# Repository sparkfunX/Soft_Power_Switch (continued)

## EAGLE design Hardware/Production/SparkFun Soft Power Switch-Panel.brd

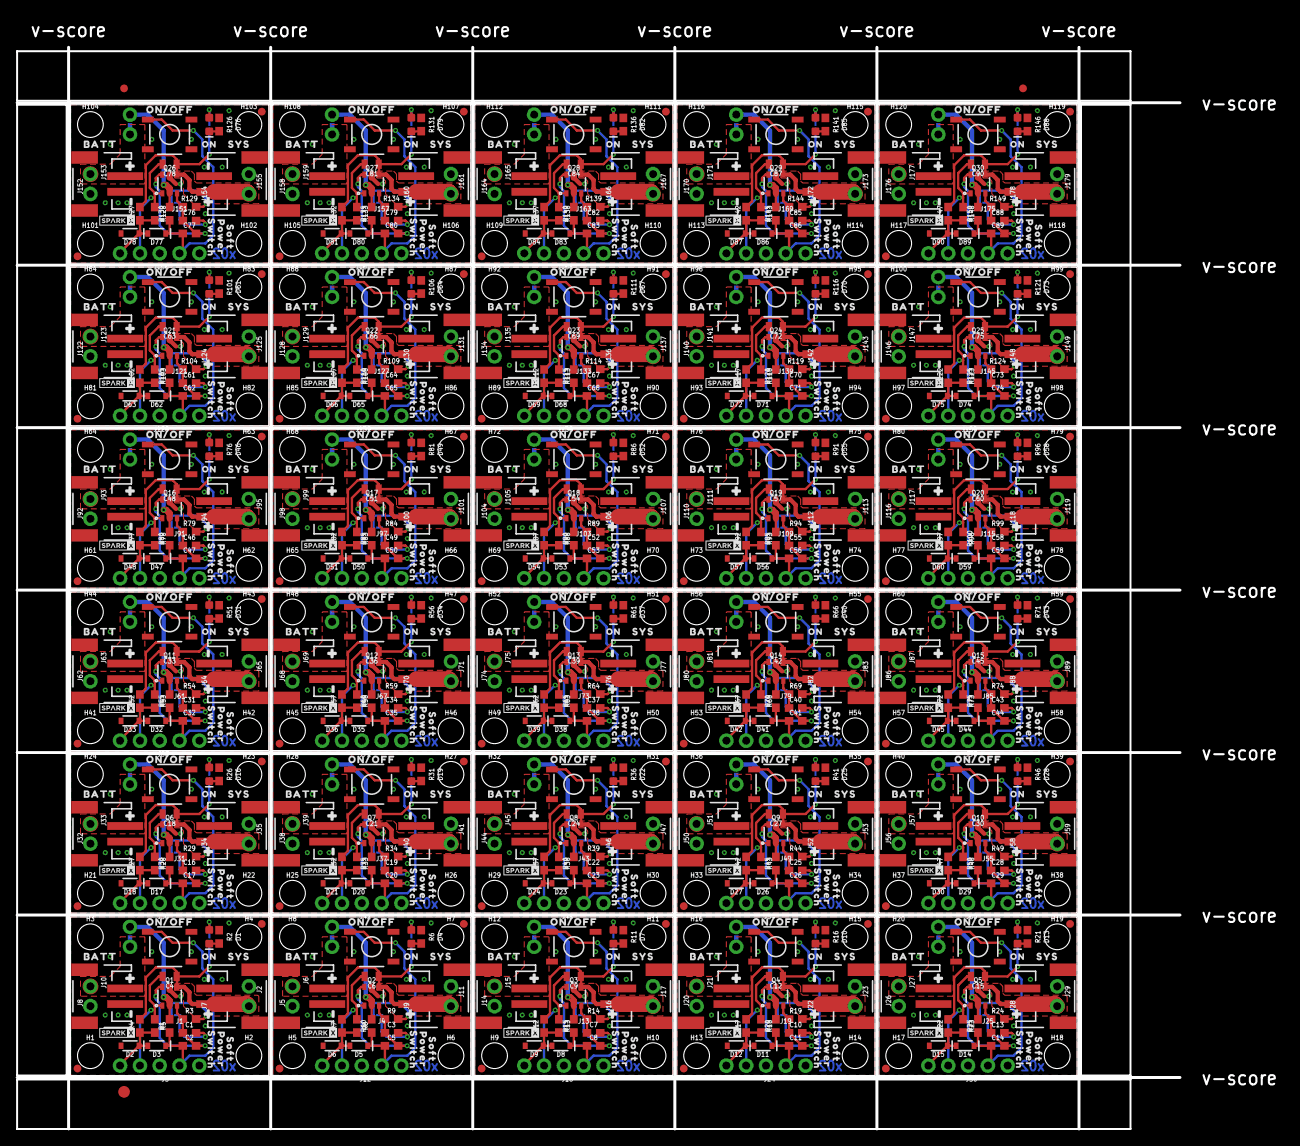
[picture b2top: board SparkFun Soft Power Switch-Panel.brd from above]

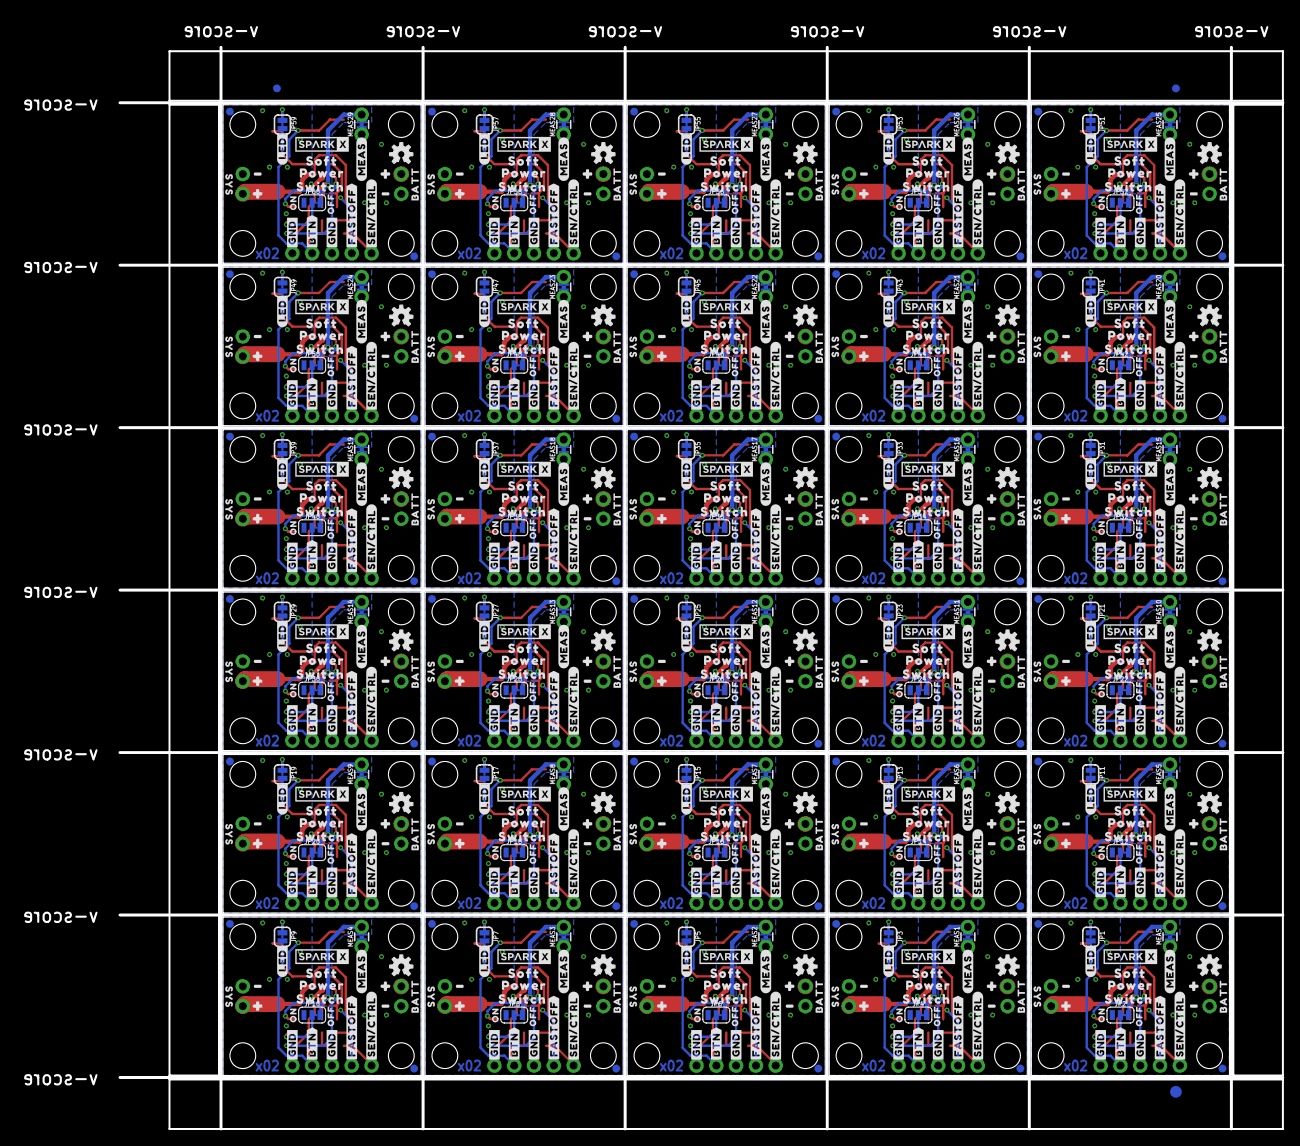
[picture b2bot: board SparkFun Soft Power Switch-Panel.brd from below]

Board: 2 copper layers, 149.1 x 138.7 mm, 1866 parts (753 on the bottom side), 330 nets.

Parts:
C1, C2, C3, C5, C7, C8, C10, C11, C13, C14, C16, C17, C19, C20, C22, C23, C25, C26, C28, C29, C31, C32, C34, C35, C37, C38, C40, C41, C43, C44, C46, C47, C49, C50, C52, C53, C55, C56, C58, C59, C61, C62, C64, C65, C67, C68, C70, C71, C73, C74, C76, C77, C79, C80, C82, C83, C85, C86, C88, C89: 0.1uF; 0603
C4, C6, C9, C12, C15, C18, C21, C24, C27, C30, C33, C36, C39, C42, C45, C48, C51, C54, C57, C60, C63, C66, C69, C72, C75, C78, C81, C84, C87, C90: 22uF; 0805
D1, D4, D7, D10, D13, D16, D19, D22, D25, D28, D31, D34, D37, D40, D43, D46, D49, D52, D55, D58, D61, D64, D67, D70, D73, D76, D79, D82, D85, D88: Power; LED-0603
D2, D6, D9, D12, D15, D18, D21, D24, D27, D30, D33, D36, D39, D42, D45, D48, D51, D54, D57, D60, D63, D66, D69, D72, D75, D78, D81, D84, D87, D90: 3.3V; SOD-323
D3, D5, D8, D11, D14, D17, D20, D23, D26, D29, D32, D35, D38, D41, D44, D47, D50, D53, D56, D59, D62, D65, D68, D71, D74, D77, D80, D83, D86, D89: 250mA/100V; SOD-323
E$1, E$2, E$3, E$4: FIDUCIAL-1X2
E$5, E$6: FIDUCIAL-1.5X3
FD1, FD2, FD3, FD4, FD5, FD6, FD7, FD8, FD9, FD10, FD11, FD12, FD13, FD14, FD15, FD16, FD17, FD18, FD19, FD20, FD21, FD22, FD23, FD24, FD25, FD26, FD27, FD28, FD29, FD30, FD31, FD32, FD33, FD34, FD35, FD36, FD37, FD38, FD39, FD40, FD41, FD42, FD43, FD44, FD45, FD46, FD47, FD48, FD49, FD50, FD51, FD52, FD53, FD54, FD55, FD56, FD57, FD58, FD59, FD60, FD61, FD62, FD63, FD64, FD65, FD66, FD67, FD68, FD69, FD70, FD71, FD72, FD73, FD74, FD75, FD76, FD77, FD78, FD79, FD80, FD81, FD82, FD83, FD84, FD85, FD86, FD87, FD88, FD89, FD90, FD91, FD92, FD93, FD94, FD95, FD96, FD97, FD98, FD99, FD100, FD101, FD102, FD103, FD104, FD105, FD106, FD107, FD108, FD109, FD110, FD111, FD112, FD113, FD114, FD115, FD116, FD117, FD118, FD119, FD120: FIDUCIAL1X2; FIDUCIAL-1X2
H1, H2, H3, H4, H5, H6, H7, H8, H9, H10, H11, H12, H13, H14, H15, H16, H17, H18, H19, H20, H21, H22, H23, H24, H25, H26, H27, H28, H29, H30, H31, H32, H33, H34, H35, H36, H37, H38, H39, H40, H41, H42, H43, H44, H45, H46, H47, H48, H49, H50, H51, H52, H53, H54, H55, H56, H57, H58, H59, H60, H61, H62, H63, H64, H65, H66, H67, H68, H69, H70, H71, H72, H73, H74, H75, H76, H77, H78, H79, H80, H81, H82, H83, H84, H85, H86, H87, H88, H89, H90, H91, H92, H93, H94, H95, H96, H97, H98, H99, H100, H101, H102, H103, H104, H105, H106, H107, H108, H109, H110, H111, H112, H113, H114, H115, H116, H117, H118, H119, H120: STAND-OFF
J1, J4, J13, J19, J25, J31, J37, J43, J49, J55, J61, J67, J73, J79, J85, J91, J97, J103, J109, J115, J121, J127, J133, J139, J145, J151, J157, J163, J169, J175: Ext Button; 1X02_NO_SILK
J2, J5, J8, J11, J14, J17, J20, J23, J26, J29, J32, J35, J38, J41, J44, J47, J50, J53, J56, J59, J62, J65, J68, J71, J74, J77, J80, J83, J86, J89, J92, J95, J98, J101, J104, J107, J110, J113, J116, J119, J122, J125, J128, J131, J134, J137, J140, J143, J146, J149, J152, J155, J158, J161, J164, J167, J170, J173, J176, J179: JST-2-SMD
J3, J12, J18, J24, J30, J36, J42, J48, J54, J60, J66, J72, J78, J84, J90, J96, J102, J108, J114, J120, J126, J132, J138, J144, J150, J156, J162, J168, J174, J180: 1X03_NO_SILK
J6, J10, J15, J21, J27, J33, J39, J45, J51, J57, J63, J69, J75, J81, J87, J93, J99, J105, J111, J117, J123, J129, J135, J141, J147, J153, J159, J165, J171, J177: 1X02_NO_SILK
J7, J9, J16, J22, J28, J34, J40, J46, J52, J58, J64, J70, J76, J82, J88, J94, J100, J106, J112, J118, J124, J130, J136, J142, J148, J154, J160, J166, J172, J178: System Power; 1X02_NO_SILK
JP1, JP3, JP5, JP7, JP9, JP11, JP13, JP15, JP17, JP19, JP21, JP23, JP25, JP27, JP29, JP31, JP33, JP35, JP37, JP39, JP41, JP43, JP45, JP47, JP49, JP51, JP53, JP55, JP57, JP59: SMT-JUMPER_2_NC_TRACE_SILK
JP2, JP4, JP6, JP8, JP10, JP12, JP14, JP16, JP18, JP20, JP22, JP24, JP26, JP28, JP30, JP32, JP34, JP36, JP38, JP40, JP42, JP44, JP46, JP48, JP50, JP52, JP54, JP56, JP58, JP60: SMT-JUMPER_3_1-NC_TRACE_SILK
LOGO1, LOGO2, LOGO3, LOGO4, LOGO5, LOGO6, LOGO7, LOGO8, LOGO9, LOGO10, LOGO11, LOGO12, LOGO13, LOGO14, LOGO15, LOGO16, LOGO17, LOGO18, LOGO19, LOGO20, LOGO21, LOGO22, LOGO23, LOGO24, LOGO25, LOGO26, LOGO27, LOGO28, LOGO29, LOGO30: OSHW-LOGOS; OSHW-LOGO-S
MEAS, MEAS1, MEAS2, MEAS3, MEAS4, MEAS5, MEAS6, MEAS7, MEAS8, MEAS9, MEAS10, MEAS11, MEAS12, MEAS13, MEAS14, MEAS15, MEAS16, MEAS17, MEAS18, MEAS19, MEAS20, MEAS21, MEAS22, MEAS23, MEAS24, MEAS25, MEAS26, MEAS27, MEAS28, MEAS29: COMBO-JUMPER_2_NC_TRACE
Q1, Q2, Q3, Q4, Q5, Q6, Q7, Q8, Q9, Q10, Q11, Q12, Q13, Q14, Q15, Q16, Q17, Q18, Q19, Q20, Q21, Q22, Q23, Q24, Q25, Q26, Q27, Q28, Q29, Q30: SIL2308-TP; SOT26
R1, R4, R7, R10, R12, R15, R17, R20, R22, R25, R27, R30, R32, R35, R37, R40, R42, R45, R47, R50, R52, R55, R57, R60, R62, R65, R67, R70, R72, R75, R77, R80, R82, R85, R87, R90, R92, R95, R97, R100, R102, R105, R107, R110, R112, R115, R117, R120, R122, R125, R127, R130, R132, R135, R137, R140, R142, R145, R147, R150: 10k; 0603
R2, R6, R11, R16, R21, R26, R31, R36, R41, R46, R51, R56, R61, R66, R71, R76, R81, R86, R91, R96, R101, R106, R111, R116, R121, R126, R131, R136, R141, R146: 1k; 0603
R3, R9, R14, R19, R24, R29, R34, R39, R44, R49, R54, R59, R64, R69, R74, R79, R84, R89, R94, R99, R104, R109, R114, R119, R124, R129, R134, R139, R144, R149: 100k; 0603
R5, R8, R13, R18, R23, R28, R33, R38, R43, R48, R53, R58, R63, R68, R73, R78, R83, R88, R93, R98, R103, R108, R113, R118, R123, R128, R133, R138, R143, R148: 300k; 0603
S1, S2, S3, S4, S5, S6, S7, S8, S9, S10, S11, S12, S13, S14, S15, S16, S17, S18, S19, S20, S21, S22, S23, S24, S25, S26, S27, S28, S29, S30: Power; TACTILE_SWITCH_SMD_5.2MM
U$1, U$32, U$63, U$94, U$125, U$156, U$187, U$218, U$249, U$280, U$311, U$342, U$373, U$404, U$435, U$466, U$497, U$528, U$559, U$590, U$621, U$652, U$683, U$714, U$745, U$776, U$807, U$838, U$869, U$900: SPARKX-LOGO3; SPARKX-SMALL
U$2, U$33, U$64, U$95, U$126, U$157, U$188, U$219, U$250, U$281, U$312, U$343, U$374, U$405, U$436, U$467, U$498, U$529, U$560, U$591, U$622, U$653, U$684, U$715, U$746, U$777, U$808, U$839, U$870, U$901: #BTN#2
U$3, U$4, U$34, U$35, U$65, U$66, U$96, U$97, U$127, U$128, U$158, U$159, U$189, U$190, U$220, U$221, U$251, U$252, U$282, U$283, U$313, U$314, U$344, U$345, U$375, U$376, U$406, U$407, U$437, U$438, U$468, U$469, U$499, U$500, U$530, U$531, U$561, U$562, U$592, U$593, U$623, U$624, U$654, U$655, U$685, U$686, U$716, U$717, U$747, U$748, U$778, U$779, U$809, U$810, U$840, U$841, U$871, U$872, U$902, U$903: #GND#0
U$5, U$36, U$67, U$98, U$129, U$160, U$191, U$222, U$253, U$284, U$315, U$346, U$377, U$408, U$439, U$470, U$501, U$532, U$563, U$594, U$625, U$656, U$687, U$718, U$749, U$780, U$811, U$842, U$873, U$904: #SEN#CTRL#1
U$6, U$37, U$68, U$99, U$130, U$161, U$192, U$223, U$254, U$285, U$316, U$347, U$378, U$409, U$440, U$471, U$502, U$533, U$564, U$595, U$626, U$657, U$688, U$719, U$750, U$781, U$812, U$843, U$874, U$905: ON#OFF0
U$7, U$29, U$38, U$60, U$69, U$91, U$100, U$122, U$131, U$153, U$162, U$184, U$193, U$215, U$224, U$246, U$255, U$277, U$286, U$308, U$317, U$339, U$348, U$370, U$379, U$401, U$410, U$432, U$441, U$463, U$472, U$494, U$503, U$525, U$534, U$556, U$565, U$587, U$596, U$618, U$627, U$649, U$658, U$680, U$689, U$711, U$720, U$742, U$751, U$773, U$782, U$804, U$813, U$835, U$844, U$866, U$875, U$897, U$906, U$928: BATT0
U$8, U$31, U$39, U$61, U$70, U$92, U$101, U$123, U$132, U$154, U$163, U$185, U$194, U$216, U$225, U$247, U$256, U$278, U$287, U$309, U$318, U$340, U$349, U$371, U$380, U$402, U$411, U$433, U$442, U$464, U$473, U$495, U$504, U$526, U$535, U$557, U$566, U$588, U$597, U$619, U$628, U$650, U$659, U$681, U$690, U$712, U$721, U$743, U$752, U$774, U$783, U$805, U$814, U$836, U$845, U$867, U$876, U$898, U$907, U$929: SYS1
U$9, U$10, U$14, U$22, U$40, U$41, U$48, U$50, U$71, U$72, U$79, U$81, U$102, U$103, U$110, U$112, U$133, U$134, U$141, U$143, U$164, U$165, U$172, U$174, U$195, U$196, U$203, U$205, U$226, U$227, U$234, U$236, U$257, U$258, U$265, U$267, U$288, U$289, U$296, U$298, U$319, U$320, U$327, U$329, U$350, U$351, U$358, U$360, U$381, U$382, U$389, U$391, U$412, U$413, U$420, U$422, U$443, U$444, U$451, U$453, U$474, U$475, U$482, U$484, U$505, U$506, U$513, U$515, U$536, U$537, U$544, U$546, U$567, U$568, U$575, U$577, U$598, U$599, U$606, U$608, U$629, U$630, U$637, U$639, U$660, U$661, U$668, U$670, U$691, U$692, U$699, U$701, U$722, U$723, U$730, U$732, U$753, U$754, U$761, U$763, U$784, U$785, U$792, U$794, U$815, U$816, U$823, U$825, U$846, U$847, U$854, U$856, U$877, U$878, U$885, U$887, U$908, U$909, U$916, U$918: #0
U$11, U$12, U$20, U$23, U$42, U$43, U$49, U$51, U$73, U$74, U$80, U$82, U$104, U$105, U$111, U$113, U$135, U$136, U$142, U$144, U$166, U$167, U$173, U$175, U$197, U$198, U$204, U$206, U$228, U$229, U$235, U$237, U$259, U$260, U$266, U$268, U$290, U$291, U$297, U$299, U$321, U$322, U$328, U$330, U$352, U$353, U$359, U$361, U$383, U$384, U$390, U$392, U$414, U$415, U$421, U$423, U$445, U$446, U$452, U$454, U$476, U$477, U$483, U$485, U$507, U$508, U$514, U$516, U$538, U$539, U$545, U$547, U$569, U$570, U$576, U$578, U$600, U$601, U$607, U$609, U$631, U$632, U$638, U$640, U$662, U$663, U$669, U$671, U$693, U$694, U$700, U$702, U$724, U$725, U$731, U$733, U$755, U$756, U$762, U$764, U$786, U$787, U$793, U$795, U$817, U$818, U$824, U$826, U$848, U$849, U$855, U$857, U$879, U$880, U$886, U$888, U$910, U$911, U$917, U$919: #1
U$13, U$44, U$75, U$106, U$137, U$168, U$199, U$230, U$261, U$292, U$323, U$354, U$385, U$416, U$447, U$478, U$509, U$540, U$571, U$602, U$633, U$664, U$695, U$726, U$757, U$788, U$819, U$850, U$881, U$912: #MEAS#0
U$15, U$62, U$93, U$124, U$155, U$186, U$217, U$248, U$279, U$310, U$341, U$372, U$403, U$434, U$465, U$496, U$527, U$558, U$589, U$620, U$651, U$682, U$713, U$744, U$775, U$806, U$837, U$868, U$899, U$930: SPARKX-LOGO2; SPARKX-TINY
U$16, U$57, U$88, U$119, U$150, U$181, U$212, U$243, U$274, U$305, U$336, U$367, U$398, U$429, U$460, U$491, U$522, U$553, U$584, U$615, U$646, U$677, U$708, U$739, U$770, U$801, U$832, U$863, U$894, U$925: OFF1
U$17, U$45, U$76, U$107, U$138, U$169, U$200, U$231, U$262, U$293, U$324, U$355, U$386, U$417, U$448, U$479, U$510, U$541, U$572, U$603, U$634, U$665, U$696, U$727, U$758, U$789, U$820, U$851, U$882, U$913: SWITCH2
U$18, U$25, U$46, U$58, U$77, U$89, U$108, U$120, U$139, U$151, U$170, U$182, U$201, U$213, U$232, U$244, U$263, U$275, U$294, U$306, U$325, U$337, U$356, U$368, U$387, U$399, U$418, U$430, U$449, U$461, U$480, U$492, U$511, U$523, U$542, U$554, U$573, U$585, U$604, U$616, U$635, U$647, U$666, U$678, U$697, U$709, U$728, U$740, U$759, U$771, U$790, U$802, U$821, U$833, U$852, U$864, U$883, U$895, U$914, U$926: ON0
U$19, U$47, U$78, U$109, U$140, U$171, U$202, U$233, U$264, U$295, U$326, U$357, U$388, U$419, U$450, U$481, U$512, U$543, U$574, U$605, U$636, U$667, U$698, U$729, U$760, U$791, U$822, U$853, U$884, U$915: #LED#0
U$21, U$55, U$86, U$117, U$148, U$179, U$210, U$241, U$272, U$303, U$334, U$365, U$396, U$427, U$458, U$489, U$520, U$551, U$582, U$613, U$644, U$675, U$706, U$737, U$768, U$799, U$830, U$861, U$892, U$923: SOFT_0
U$24, U$56, U$87, U$118, U$149, U$180, U$211, U$242, U$273, U$304, U$335, U$366, U$397, U$428, U$459, U$490, U$521, U$552, U$583, U$614, U$645, U$676, U$707, U$738, U$769, U$800, U$831, U$862, U$893, U$924: POWER_1
U$26, U$59, U$90, U$121, U$152, U$183, U$214, U$245, U$276, U$307, U$338, U$369, U$400, U$431, U$462, U$493, U$524, U$555, U$586, U$617, U$648, U$679, U$710, U$741, U$772, U$803, U$834, U$865, U$896, U$927: #FASTOFF#0
U$27, U$52, U$83, U$114, U$145, U$176, U$207, U$238, U$269, U$300, U$331, U$362, U$393, U$424, U$455, U$486, U$517, U$548, U$579, U$610, U$641, U$672, U$703, U$734, U$765, U$796, U$827, U$858, U$889, U$920: SOFT0
U$28, U$53, U$84, U$115, U$146, U$177, U$208, U$239, U$270, U$301, U$332, U$363, U$394, U$425, U$456, U$487, U$518, U$549, U$580, U$611, U$642, U$673, U$704, U$735, U$766, U$797, U$828, U$859, U$890, U$921: POWER1
U$30, U$54, U$85, U$116, U$147, U$178, U$209, U$240, U$271, U$302, U$333, U$364, U$395, U$426, U$457, U$488, U$519, U$550, U$581, U$612, U$643, U$674, U$705, U$736, U$767, U$798, U$829, U$860, U$891, U$922: SWITCH_2

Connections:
FAST_OFF: C4.2, J3.2, Q1.G1, R5.1
FAST_OFF1: C6.2, J12.2, Q2.G1, R8.1
FAST_OFF2: C9.2, J18.2, Q3.G1, R13.1
FAST_OFF3: C12.2, J24.2, Q4.G1, R18.1
FAST_OFF4: C15.2, J30.2, Q5.G1, R23.1
FAST_OFF5: C18.2, J36.2, Q6.G1, R28.1
FAST_OFF6: C21.2, J42.2, Q7.G1, R33.1
FAST_OFF7: C24.2, J48.2, Q8.G1, R38.1
FAST_OFF8: C27.2, J54.2, Q9.G1, R43.1
FAST_OFF9: C30.2, J60.2, Q10.G1, R48.1
FAST_OFF10: C33.2, J66.2, Q11.G1, R53.1
FAST_OFF11: C36.2, J72.2, Q12.G1, R58.1
FAST_OFF12: C39.2, J78.2, Q13.G1, R63.1
FAST_OFF13: C42.2, J84.2, Q14.G1, R68.1
FAST_OFF14: C45.2, J90.2, Q15.G1, R73.1
FAST_OFF15: C48.2, J96.2, Q16.G1, R78.1
FAST_OFF16: C51.2, J102.2, Q17.G1, R83.1
FAST_OFF17: C54.2, J108.2, Q18.G1, R88.1
FAST_OFF18: C57.2, J114.2, Q19.G1, R93.1
FAST_OFF19: C60.2, J120.2, Q20.G1, R98.1
FAST_OFF20: C63.2, J126.2, Q21.G1, R103.1
FAST_OFF21: C66.2, J132.2, Q22.G1, R108.1
FAST_OFF22: C69.2, J138.2, Q23.G1, R113.1
FAST_OFF23: C72.2, J144.2, Q24.G1, R118.1
FAST_OFF24: C75.2, J150.2, Q25.G1, R123.1
FAST_OFF25: C78.2, J156.2, Q26.G1, R128.1
FAST_OFF26: C81.2, J162.2, Q27.G1, R133.1
FAST_OFF27: C84.2, J168.2, Q28.G1, R138.1
FAST_OFF28: C87.2, J174.2, Q29.G1, R143.1
FAST_OFF29: C90.2, J180.2, Q30.G1, R148.1
GND: D2.A, J1.2, J2.1, J3.1, J7.2, J8.1, J10.2, JP2.1, Q1.S1, R2.1, S1.3
GND1: D6.A, J4.2, J5.1, J6.2, J9.2, J11.1, J12.1, JP4.1, Q2.S1, R6.1, S2.3
GND2: D9.A, J13.2, J14.1, J15.2, J16.2, J17.1, J18.1, JP6.1, Q3.S1, R11.1, S3.3
GND3: D12.A, J19.2, J20.1, J21.2, J22.2, J23.1, J24.1, JP8.1, Q4.S1, R16.1, S4.3
GND4: D15.A, J25.2, J26.1, J27.2, J28.2, J29.1, J30.1, JP10.1, Q5.S1, R21.1, S5.3
GND5: D18.A, J31.2, J32.1, J33.2, J34.2, J35.1, J36.1, JP12.1, Q6.S1, R26.1, S6.3
GND6: D21.A, J37.2, J38.1, J39.2, J40.2, J41.1, J42.1, JP14.1, Q7.S1, R31.1, S7.3
GND7: D24.A, J43.2, J44.1, J45.2, J46.2, J47.1, J48.1, JP16.1, Q8.S1, R36.1, S8.3
GND8: D27.A, J49.2, J50.1, J51.2, J52.2, J53.1, J54.1, JP18.1, Q9.S1, R41.1, S9.3
GND9: D30.A, J55.2, J56.1, J57.2, J58.2, J59.1, J60.1, JP20.1, Q10.S1, R46.1, S10.3
GND10: D33.A, J61.2, J62.1, J63.2, J64.2, J65.1, J66.1, JP22.1, Q11.S1, R51.1, S11.3
GND11: D36.A, J67.2, J68.1, J69.2, J70.2, J71.1, J72.1, JP24.1, Q12.S1, R56.1, S12.3
GND12: D39.A, J73.2, J74.1, J75.2, J76.2, J77.1, J78.1, JP26.1, Q13.S1, R61.1, S13.3
GND13: D42.A, J79.2, J80.1, J81.2, J82.2, J83.1, J84.1, JP28.1, Q14.S1, R66.1, S14.3
GND14: D45.A, J85.2, J86.1, J87.2, J88.2, J89.1, J90.1, JP30.1, Q15.S1, R71.1, S15.3
GND15: D48.A, J91.2, J92.1, J93.2, J94.2, J95.1, J96.1, JP32.1, Q16.S1, R76.1, S16.3
GND16: D51.A, J97.2, J98.1, J99.2, J100.2, J101.1, J102.1, JP34.1, Q17.S1, R81.1, S17.3
GND17: D54.A, J103.2, J104.1, J105.2, J106.2, J107.1, J108.1, JP36.1, Q18.S1, R86.1, S18.3
GND18: D57.A, J109.2, J110.1, J111.2, J112.2, J113.1, J114.1, JP38.1, Q19.S1, R91.1, S19.3
GND19: D60.A, J115.2, J116.1, J117.2, J118.2, J119.1, J120.1, JP40.1, Q20.S1, R96.1, S20.3
GND20: D63.A, J121.2, J122.1, J123.2, J124.2, J125.1, J126.1, JP42.1, Q21.S1, R101.1, S21.3
GND21: D66.A, J127.2, J128.1, J129.2, J130.2, J131.1, J132.1, JP44.1, Q22.S1, R106.1, S22.3
GND22: D69.A, J133.2, J134.1, J135.2, J136.2, J137.1, J138.1, JP46.1, Q23.S1, R111.1, S23.3
GND23: D72.A, J139.2, J140.1, J141.2, J142.2, J143.1, J144.1, JP48.1, Q24.S1, R116.1, S24.3
GND24: D75.A, J145.2, J146.1, J147.2, J148.2, J149.1, J150.1, JP50.1, Q25.S1, R121.1, S25.3
GND25: D78.A, J151.2, J152.1, J153.2, J154.2, J155.1, J156.1, JP52.1, Q26.S1, R126.1, S26.3
GND26: D81.A, J157.2, J158.1, J159.2, J160.2, J161.1, J162.1, JP54.1, Q27.S1, R131.1, S27.3
GND27: D84.A, J163.2, J164.1, J165.2, J166.2, J167.1, J168.1, JP56.1, Q28.S1, R136.1, S28.3
GND28: D87.A, J169.2, J170.1, J171.2, J172.2, J173.1, J174.1, JP58.1, Q29.S1, R141.1, S29.3
GND29: D90.A, J175.2, J176.1, J177.2, J178.2, J179.1, J180.1, JP60.1, Q30.S1, R146.1, S30.3
unnamed: C1.2, JP2.2
unnamed: D1.A, JP1.1
unnamed: D4.C, R6.2
unnamed: C3.1, C5.2, Q2.D1, Q2.G2, R9.1
unnamed: D4.A, JP3.1
unnamed: D1.C, R2.2
unnamed: C3.2, JP4.2
unnamed: D7.C, R11.2
unnamed: C7.1, C8.2, Q3.D1, Q3.G2, R14.1
unnamed: D7.A, JP5.1
unnamed: C7.2, JP6.2
unnamed: D10.C, R16.2
unnamed: C10.1, C11.2, Q4.D1, Q4.G2, R19.1
unnamed: D10.A, JP7.1
unnamed: C1.1, C2.2, Q1.D1, Q1.G2, R3.1
unnamed: C10.2, JP8.2
unnamed: D13.C, R21.2
unnamed: C13.1, C14.2, Q5.D1, Q5.G2, R24.1
unnamed: D13.A, JP9.1
unnamed: C13.2, JP10.2
unnamed: D16.C, R26.2
unnamed: C16.1, C17.2, Q6.D1, Q6.G2, R29.1
unnamed: D16.A, JP11.1
unnamed: C16.2, JP12.2
unnamed: D19.C, R31.2
unnamed: C19.1, C20.2, Q7.D1, Q7.G2, R34.1
unnamed: D19.A, JP13.1
unnamed: C19.2, JP14.2
unnamed: D22.C, R36.2
unnamed: C22.1, C23.2, Q8.D1, Q8.G2, R39.1
unnamed: D22.A, JP15.1
unnamed: C22.2, JP16.2
unnamed: D25.C, R41.2
unnamed: C25.1, C26.2, Q9.D1, Q9.G2, R44.1
unnamed: D25.A, JP17.1
unnamed: C25.2, JP18.2
unnamed: D28.C, R46.2
unnamed: C28.1, C29.2, Q10.D1, Q10.G2, R49.1
unnamed: D28.A, JP19.1
unnamed: C28.2, JP20.2
unnamed: D31.C, R51.2
unnamed: C31.1, C32.2, Q11.D1, Q11.G2, R54.1
unnamed: D31.A, JP21.1
unnamed: C31.2, JP22.2
unnamed: D34.C, R56.2
unnamed: C34.1, C35.2, Q12.D1, Q12.G2, R59.1
unnamed: D34.A, JP23.1
unnamed: C34.2, JP24.2
unnamed: D37.C, R61.2
unnamed: C37.1, C38.2, Q13.D1, Q13.G2, R64.1
unnamed: D37.A, JP25.1
unnamed: C37.2, JP26.2
unnamed: D40.C, R66.2
unnamed: C40.1, C41.2, Q14.D1, Q14.G2, R69.1
unnamed: D40.A, JP27.1
unnamed: C40.2, JP28.2
unnamed: D43.C, R71.2
unnamed: C43.1, C44.2, Q15.D1, Q15.G2, R74.1
unnamed: D43.A, JP29.1
unnamed: C43.2, JP30.2
unnamed: D46.C, R76.2
unnamed: C46.1, C47.2, Q16.D1, Q16.G2, R79.1
unnamed: D46.A, JP31.1
unnamed: C46.2, JP32.2
unnamed: D49.C, R81.2
unnamed: C49.1, C50.2, Q17.D1, Q17.G2, R84.1
unnamed: D49.A, JP33.1
unnamed: C49.2, JP34.2
unnamed: D52.C, R86.2
unnamed: C52.1, C53.2, Q18.D1, Q18.G2, R89.1
unnamed: D52.A, JP35.1
unnamed: C52.2, JP36.2
unnamed: D55.C, R91.2
unnamed: C55.1, C56.2, Q19.D1, Q19.G2, R94.1
unnamed: D55.A, JP37.1
unnamed: C55.2, JP38.2
unnamed: D58.C, R96.2
unnamed: C58.1, C59.2, Q20.D1, Q20.G2, R99.1
unnamed: D58.A, JP39.1
unnamed: C58.2, JP40.2
unnamed: D61.C, R101.2
unnamed: C61.1, C62.2, Q21.D1, Q21.G2, R104.1
unnamed: D61.A, JP41.1
unnamed: C61.2, JP42.2
unnamed: D64.C, R106.2
unnamed: C64.1, C65.2, Q22.D1, Q22.G2, R109.1
unnamed: D64.A, JP43.1
unnamed: C64.2, JP44.2
unnamed: D67.C, R111.2
unnamed: C67.1, C68.2, Q23.D1, Q23.G2, R114.1
unnamed: D67.A, JP45.1
unnamed: C67.2, JP46.2
unnamed: D70.C, R116.2
unnamed: C70.1, C71.2, Q24.D1, Q24.G2, R119.1
unnamed: D70.A, JP47.1
unnamed: C70.2, JP48.2
unnamed: D73.C, R121.2
unnamed: C73.1, C74.2, Q25.D1, Q25.G2, R124.1
unnamed: D73.A, JP49.1
unnamed: C73.2, JP50.2
unnamed: D76.C, R126.2
unnamed: C76.1, C77.2, Q26.D1, Q26.G2, R129.1
unnamed: D76.A, JP51.1
unnamed: C76.2, JP52.2
unnamed: D79.C, R131.2
unnamed: C79.1, C80.2, Q27.D1, Q27.G2, R134.1
unnamed: D79.A, JP53.1
unnamed: C79.2, JP54.2
unnamed: D82.C, R136.2
unnamed: C82.1, C83.2, Q28.D1, Q28.G2, R139.1
unnamed: D82.A, JP55.1
unnamed: C82.2, JP56.2
unnamed: D85.C, R141.2
unnamed: C85.1, C86.2, Q29.D1, Q29.G2, R144.1
unnamed: D85.A, JP57.1
unnamed: C85.2, JP58.2
unnamed: D88.C, R146.2
unnamed: C88.1, C89.2, Q30.D1, Q30.G2, R149.1
unnamed: D88.A, JP59.1
unnamed: C88.2, JP60.2
POWER_BTN: C2.1, D3.C, J1.1, R1.1, S1.1
POWER_BTN1: C5.1, D5.C, J4.1, R10.1, S2.1
POWER_BTN2: C8.1, D8.C, J13.1, R15.1, S3.1
POWER_BTN3: C11.1, D11.C, J19.1, R20.1, S4.1
POWER_BTN4: C14.1, D14.C, J25.1, R25.1, S5.1
POWER_BTN5: C17.1, D17.C, J31.1, R30.1, S6.1
POWER_BTN6: C20.1, D20.C, J37.1, R35.1, S7.1
POWER_BTN7: C23.1, D23.C, J43.1, R40.1, S8.1
POWER_BTN8: C26.1, D26.C, J49.1, R45.1, S9.1
POWER_BTN9: C29.1, D29.C, J55.1, R50.1, S10.1
POWER_BTN10: C32.1, D32.C, J61.1, R55.1, S11.1
POWER_BTN11: C35.1, D35.C, J67.1, R60.1, S12.1
POWER_BTN12: C38.1, D38.C, J73.1, R65.1, S13.1
POWER_BTN13: C41.1, D41.C, J79.1, R70.1, S14.1
POWER_BTN14: C44.1, D44.C, J85.1, R75.1, S15.1
POWER_BTN15: C47.1, D47.C, J91.1, R80.1, S16.1
POWER_BTN16: C50.1, D50.C, J97.1, R85.1, S17.1
POWER_BTN17: C53.1, D53.C, J103.1, R90.1, S18.1
POWER_BTN18: C56.1, D56.C, J109.1, R95.1, S19.1
POWER_BTN19: C59.1, D59.C, J115.1, R100.1, S20.1
POWER_BTN20: C62.1, D62.C, J121.1, R105.1, S21.1
POWER_BTN21: C65.1, D65.C, J127.1, R110.1, S22.1
POWER_BTN22: C68.1, D68.C, J133.1, R115.1, S23.1
POWER_BTN23: C71.1, D71.C, J139.1, R120.1, S24.1
POWER_BTN24: C74.1, D74.C, J145.1, R125.1, S25.1
POWER_BTN25: C77.1, D77.C, J151.1, R130.1, S26.1
POWER_BTN26: C80.1, D80.C, J157.1, R135.1, S27.1
POWER_BTN27: C83.1, D83.C, J163.1, R140.1, S28.1
POWER_BTN28: C86.1, D86.C, J169.1, R145.1, S29.1
POWER_BTN29: C89.1, D89.C, J175.1, R150.1, S30.1
POWER_SENSE/CTRL: D2.C, D3.A, J3.3, R4.1, R5.2
POWER_SENSE/CTRL1: D5.A, D6.C, J12.3, R7.1, R8.2
POWER_SENSE/CTRL2: D8.A, D9.C, J18.3, R12.1, R13.2
POWER_SENSE/CTRL3: D11.A, D12.C, J24.3, R17.1, R18.2
POWER_SENSE/CTRL4: D14.A, D15.C, J30.3, R22.1, R23.2
POWER_SENSE/CTRL5: D17.A, D18.C, J36.3, R27.1, R28.2
POWER_SENSE/CTRL6: D20.A, D21.C, J42.3, R32.1, R33.2
POWER_SENSE/CTRL7: D23.A, D24.C, J48.3, R37.1, R38.2
POWER_SENSE/CTRL8: D26.A, D27.C, J54.3, R42.1, R43.2
POWER_SENSE/CTRL9: D29.A, D30.C, J60.3, R47.1, R48.2
POWER_SENSE/CTRL10: D32.A, D33.C, J66.3, R52.1, R53.2
POWER_SENSE/CTRL11: D35.A, D36.C, J72.3, R57.1, R58.2
POWER_SENSE/CTRL12: D38.A, D39.C, J78.3, R62.1, R63.2
POWER_SENSE/CTRL13: D41.A, D42.C, J84.3, R67.1, R68.2
POWER_SENSE/CTRL14: D44.A, D45.C, J90.3, R72.1, R73.2
POWER_SENSE/CTRL15: D47.A, D48.C, J96.3, R77.1, R78.2
POWER_SENSE/CTRL16: D50.A, D51.C, J102.3, R82.1, R83.2
POWER_SENSE/CTRL17: D53.A, D54.C, J108.3, R87.1, R88.2
POWER_SENSE/CTRL18: D56.A, D57.C, J114.3, R92.1, R93.2
POWER_SENSE/CTRL19: D59.A, D60.C, J120.3, R97.1, R98.2
POWER_SENSE/CTRL20: D62.A, D63.C, J126.3, R102.1, R103.2
POWER_SENSE/CTRL21: D65.A, D66.C, J132.3, R107.1, R108.2
POWER_SENSE/CTRL22: D68.A, D69.C, J138.3, R112.1, R113.2
POWER_SENSE/CTRL23: D71.A, D72.C, J144.3, R117.1, R118.2
POWER_SENSE/CTRL24: D74.A, D75.C, J150.3, R122.1, R123.2
POWER_SENSE/CTRL25: D77.A, D78.C, J156.3, R127.1, R128.2
POWER_SENSE/CTRL26: D80.A, D81.C, J162.3, R132.1, R133.2
POWER_SENSE/CTRL27: D83.A, D84.C, J168.3, R137.1, R138.2
POWER_SENSE/CTRL28: D86.A, D87.C, J174.3, R142.1, R143.2
POWER_SENSE/CTRL29: D89.A, D90.C, J180.3, R147.1, R148.2
VCC: C4.1, J2.2, J7.1, JP1.2, Q1.D2, R4.2
VCC1: C6.1, J9.1, J11.2, JP3.2, Q2.D2, R7.2
VCC2: C9.1, J16.1, J17.2, JP5.2, Q3.D2, R12.2
VCC3: C12.1, J22.1, J23.2, JP7.2, Q4.D2, R17.2
VCC4: C15.1, J28.1, J29.2, JP9.2, Q5.D2, R22.2
VCC5: C18.1, J34.1, J35.2, JP11.2, Q6.D2, R27.2
VCC6: C21.1, J40.1, J41.2, JP13.2, Q7.D2, R32.2
VCC7: C24.1, J46.1, J47.2, JP15.2, Q8.D2, R37.2
VCC8: C27.1, J52.1, J53.2, JP17.2, Q9.D2, R42.2
VCC9: C30.1, J58.1, J59.2, JP19.2, Q10.D2, R47.2
VCC10: C33.1, J64.1, J65.2, JP21.2, Q11.D2, R52.2
VCC11: C36.1, J70.1, J71.2, JP23.2, Q12.D2, R57.2
VCC12: C39.1, J76.1, J77.2, JP25.2, Q13.D2, R62.2
VCC13: C42.1, J82.1, J83.2, JP27.2, Q14.D2, R67.2
VCC14: C45.1, J88.1, J89.2, JP29.2, Q15.D2, R72.2
VCC15: C48.1, J94.1, J95.2, JP31.2, Q16.D2, R77.2
VCC16: C51.1, J100.1, J101.2, JP33.2, Q17.D2, R82.2
VCC17: C54.1, J106.1, J107.2, JP35.2, Q18.D2, R87.2
VCC18: C57.1, J112.1, J113.2, JP37.2, Q19.D2, R92.2
VCC19: C60.1, J118.1, J119.2, JP39.2, Q20.D2, R97.2
VCC20: C63.1, J124.1, J125.2, JP41.2, Q21.D2, R102.2
VCC21: C66.1, J130.1, J131.2, JP43.2, Q22.D2, R107.2
VCC22: C69.1, J136.1, J137.2, JP45.2, Q23.D2, R112.2
VCC23: C72.1, J142.1, J143.2, JP47.2, Q24.D2, R117.2
VCC24: C75.1, J148.1, J149.2, JP49.2, Q25.D2, R122.2
VCC25: C78.1, J154.1, J155.2, JP51.2, Q26.D2, R127.2
VCC26: C81.1, J160.1, J161.2, JP53.2, Q27.D2, R132.2
VCC27: C84.1, J166.1, J167.2, JP55.2, Q28.D2, R137.2
VCC28: C87.1, J172.1, J173.2, JP57.2, Q29.D2, R142.2
VCC29: C90.1, J178.1, J179.2, JP59.2, Q30.D2, R147.2
V_BATT: J8.2, J10.1, MEAS.1, MEAS.3
V_BATT1: J5.2, J6.1, MEAS1.1, MEAS1.3
V_BATT2: J14.2, J15.1, MEAS2.1, MEAS2.3
V_BATT3: J20.2, J21.1, MEAS3.1, MEAS3.3
V_BATT4: J26.2, J27.1, MEAS4.1, MEAS4.3
V_BATT5: J32.2, J33.1, MEAS5.1, MEAS5.3
V_BATT6: J38.2, J39.1, MEAS6.1, MEAS6.3
V_BATT7: J44.2, J45.1, MEAS7.1, MEAS7.3
V_BATT8: J50.2, J51.1, MEAS8.1, MEAS8.3
V_BATT9: J56.2, J57.1, MEAS9.1, MEAS9.3
V_BATT10: J62.2, J63.1, MEAS10.1, MEAS10.3
V_BATT11: J68.2, J69.1, MEAS11.1, MEAS11.3
V_BATT12: J74.2, J75.1, MEAS12.1, MEAS12.3
V_BATT13: J80.2, J81.1, MEAS13.1, MEAS13.3
V_BATT14: J86.2, J87.1, MEAS14.1, MEAS14.3
V_BATT15: J92.2, J93.1, MEAS15.1, MEAS15.3
V_BATT16: J98.2, J99.1, MEAS16.1, MEAS16.3
V_BATT17: J104.2, J105.1, MEAS17.1, MEAS17.3
V_BATT18: J110.2, J111.1, MEAS18.1, MEAS18.3
V_BATT19: J116.2, J117.1, MEAS19.1, MEAS19.3
V_BATT20: J122.2, J123.1, MEAS20.1, MEAS20.3
V_BATT21: J128.2, J129.1, MEAS21.1, MEAS21.3
V_BATT22: J134.2, J135.1, MEAS22.1, MEAS22.3
V_BATT23: J140.2, J141.1, MEAS23.1, MEAS23.3
V_BATT24: J146.2, J147.1, MEAS24.1, MEAS24.3
V_BATT25: J152.2, J153.1, MEAS25.1, MEAS25.3
V_BATT26: J158.2, J159.1, MEAS26.1, MEAS26.3
V_BATT27: J164.2, J165.1, MEAS27.1, MEAS27.3
V_BATT28: J170.2, J171.1, MEAS28.1, MEAS28.3
V_BATT29: J176.2, J177.1, MEAS29.1, MEAS29.3
V_IN: JP2.3, MEAS.2, MEAS.4, Q1.S2, R1.2, R3.2
V_IN1: JP4.3, MEAS1.2, MEAS1.4, Q2.S2, R9.2, R10.2
V_IN2: JP6.3, MEAS2.2, MEAS2.4, Q3.S2, R14.2, R15.2
V_IN3: JP8.3, MEAS3.2, MEAS3.4, Q4.S2, R19.2, R20.2
V_IN4: JP10.3, MEAS4.2, MEAS4.4, Q5.S2, R24.2, R25.2
V_IN5: JP12.3, MEAS5.2, MEAS5.4, Q6.S2, R29.2, R30.2
V_IN6: JP14.3, MEAS6.2, MEAS6.4, Q7.S2, R34.2, R35.2
V_IN7: JP16.3, MEAS7.2, MEAS7.4, Q8.S2, R39.2, R40.2
V_IN8: JP18.3, MEAS8.2, MEAS8.4, Q9.S2, R44.2, R45.2
V_IN9: JP20.3, MEAS9.2, MEAS9.4, Q10.S2, R49.2, R50.2
V_IN10: JP22.3, MEAS10.2, MEAS10.4, Q11.S2, R54.2, R55.2
V_IN11: JP24.3, MEAS11.2, MEAS11.4, Q12.S2, R59.2, R60.2
V_IN12: JP26.3, MEAS12.2, MEAS12.4, Q13.S2, R64.2, R65.2
V_IN13: JP28.3, MEAS13.2, MEAS13.4, Q14.S2, R69.2, R70.2
V_IN14: JP30.3, MEAS14.2, MEAS14.4, Q15.S2, R74.2, R75.2
V_IN15: JP32.3, MEAS15.2, MEAS15.4, Q16.S2, R79.2, R80.2
V_IN16: JP34.3, MEAS16.2, MEAS16.4, Q17.S2, R84.2, R85.2
V_IN17: JP36.3, MEAS17.2, MEAS17.4, Q18.S2, R89.2, R90.2
V_IN18: JP38.3, MEAS18.2, MEAS18.4, Q19.S2, R94.2, R95.2
V_IN19: JP40.3, MEAS19.2, MEAS19.4, Q20.S2, R99.2, R100.2
V_IN20: JP42.3, MEAS20.2, MEAS20.4, Q21.S2, R104.2, R105.2
V_IN21: JP44.3, MEAS21.2, MEAS21.4, Q22.S2, R109.2, R110.2
V_IN22: JP46.3, MEAS22.2, MEAS22.4, Q23.S2, R114.2, R115.2
V_IN23: JP48.3, MEAS23.2, MEAS23.4, Q24.S2, R119.2, R120.2
V_IN24: JP50.3, MEAS24.2, MEAS24.4, Q25.S2, R124.2, R125.2
V_IN25: JP52.3, MEAS25.2, MEAS25.4, Q26.S2, R129.2, R130.2
V_IN26: JP54.3, MEAS26.2, MEAS26.4, Q27.S2, R134.2, R135.2
V_IN27: JP56.3, MEAS27.2, MEAS27.4, Q28.S2, R139.2, R140.2
V_IN28: JP58.3, MEAS28.2, MEAS28.4, Q29.S2, R144.2, R145.2
V_IN29: JP60.3, MEAS29.2, MEAS29.4, Q30.S2, R149.2, R150.2

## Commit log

2021-01-26 x02: Add fast off. Add zener protection. Increase V rating of cap. Increase cap size.
2021-01-26 Schematic compress
2021-02-08 Replace MOSFET with SIL2308-TP
2021-02-08 Remove backup files
2021-02-08 Replace MOSFET on panel.
2021-02-16 Add prod ID to power LED.
2021-04-19 Add 12VGS max note
2021-04-19 Rename example
